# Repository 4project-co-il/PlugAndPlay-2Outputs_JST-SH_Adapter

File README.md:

# PlugAndPlay: Output module with JST-SH connectors as an adapter for other devices
This is the repository with the files for PlugAndPlay output module with JST-SH connectors on output lines.

That module have 2x 3pin JST-SH connectors, each allowing control of Pololu's single relay with JST-SH connector for easy connection.
The module also have 1x 4pin JST-SH connector, allowing control of Pololu's double relay with JST-SH connector.
The 2x 3pin connectors and 1x 4pin connector are connected in parallel to the same INT lines from the PnP connector, so they should not be used together.
The PnP Power Connector is used to provide the voltage needed for the Pololu's relays. Generally 5V or 12V, depending on the relay you use.
PnP INT lines are used to control the relay's EN lines.

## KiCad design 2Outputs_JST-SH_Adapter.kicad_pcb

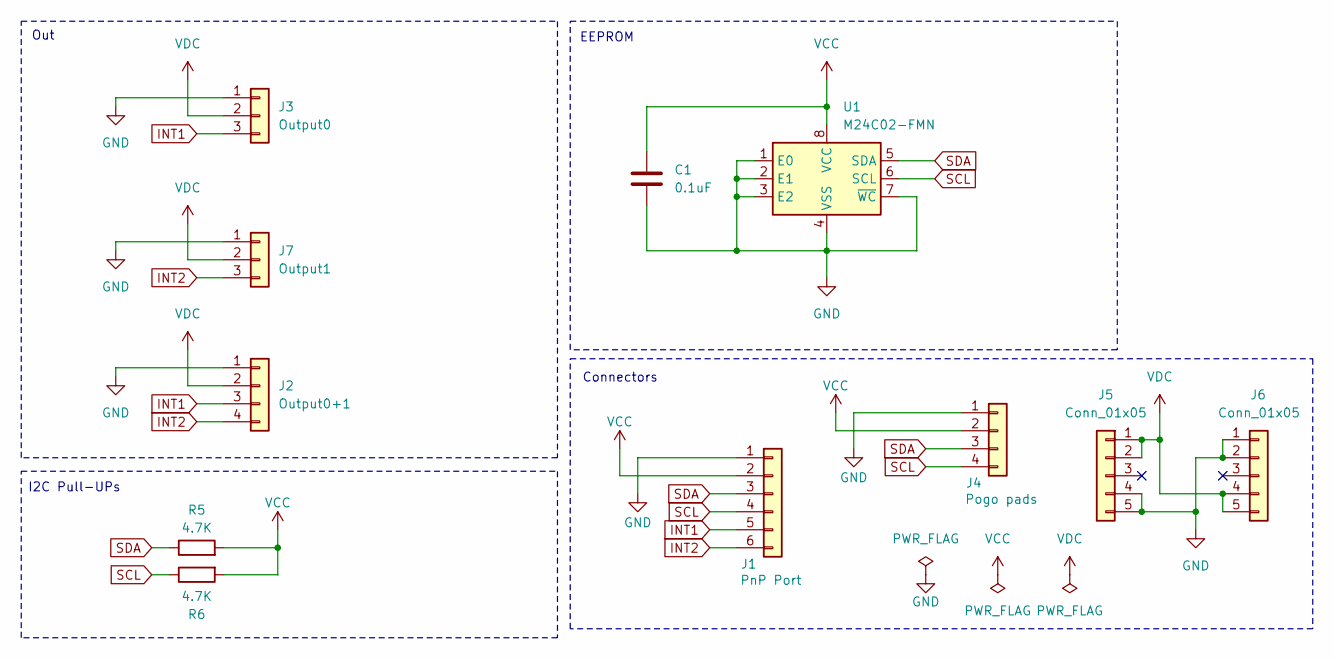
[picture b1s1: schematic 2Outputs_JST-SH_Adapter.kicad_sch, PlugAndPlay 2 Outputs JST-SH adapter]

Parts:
C1: 0.1uF; C_0603_1608Metric; MPN C14663
J1: JST_SH_SM06B-SRSS-TB_1x06-1MP_P1.00mm_Horizontal; MPN C7430448
J2: Output0+1; JST_SH_SM04B-SRSS-TB_1x04-1MP_P1.00mm_Horizontal; MPN C7430446
J3: Output0; JST_SH_SM03B-SRSS-TB_1x03-1MP_P1.00mm_Horizontal; MPN C7430445
J4: Conn_01x04; PogoPinsPads_1x04_P2.5mm
J5: Conn_01x05; PinSocket_1x05_P2.54mm_Vertical_SMD_Pin1Right; MPN RealRun
J6: Conn_01x05; PinSocket_1x05_P2.54mm_Vertical_SMD_Pin1Left; MPN RealRun
J7: Output1; JST_SH_SM03B-SRSS-TB_1x03-1MP_P1.00mm_Horizontal; MPN C7430445
R5, R6: 4.7K; R_0603_1608Metric; MPN C4190
U1: M24C02-FMN; SOIC-8_3.9x4.9mm_P1.27mm; MPN C114502

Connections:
GND: C1.2, J1.1, J2.1, J3.1, J4.1, J5.4, J5.5, J6.1, J6.2, J7.1, U1.1 (E0), U1.2 (E1), U1.3 (E2), U1.4 (VSS), U1.7 (~WC)
INT1: J1.5, J2.3, J3.3
INT2: J1.6, J2.4, J7.3
SCL: J1.4, J4.4, R6.1, U1.6 (SCL)
SDA: J1.3, J4.3, R5.1, U1.5 (SDA)
VCC: C1.1, J1.2, J4.2, R5.2, R6.2, U1.8 (VCC)
VDC: J2.2, J3.2, J5.1, J5.2, J6.4, J6.5, J7.2

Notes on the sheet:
EEPROM
Connectors
I2C Pull-UPs
Out

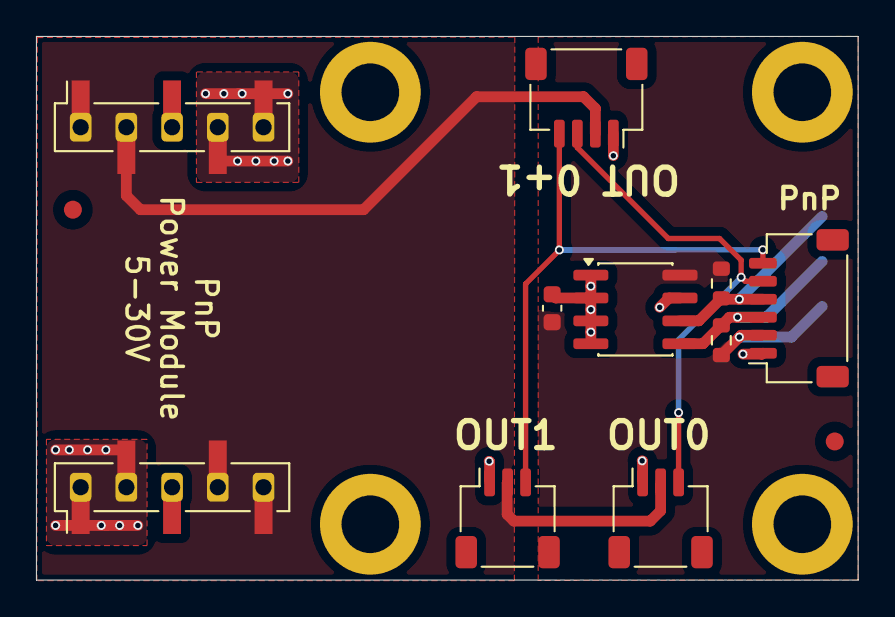
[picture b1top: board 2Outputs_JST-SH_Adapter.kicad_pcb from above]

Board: 2 copper layers, 45.6 x 30.2 mm, 11 parts (1 on the bottom side), 7 nets.
